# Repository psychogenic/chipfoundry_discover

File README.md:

# ChipFoundry ChipDiscover 2.0

ChipDiscover 2.0 is a mainboard designed to accept a variety of breakout modules (FPGA, TinyTapeout, Chipfoundry ASICs...) via an M.2 interface.

## FPGA M.2

The FPGA M.2 may be used along with [riffpga](https://github.com/psychogenic/riffpga) installed on the mainboard to allow for drag&drop bitstream loading through the USB-C connector and virtual drive.

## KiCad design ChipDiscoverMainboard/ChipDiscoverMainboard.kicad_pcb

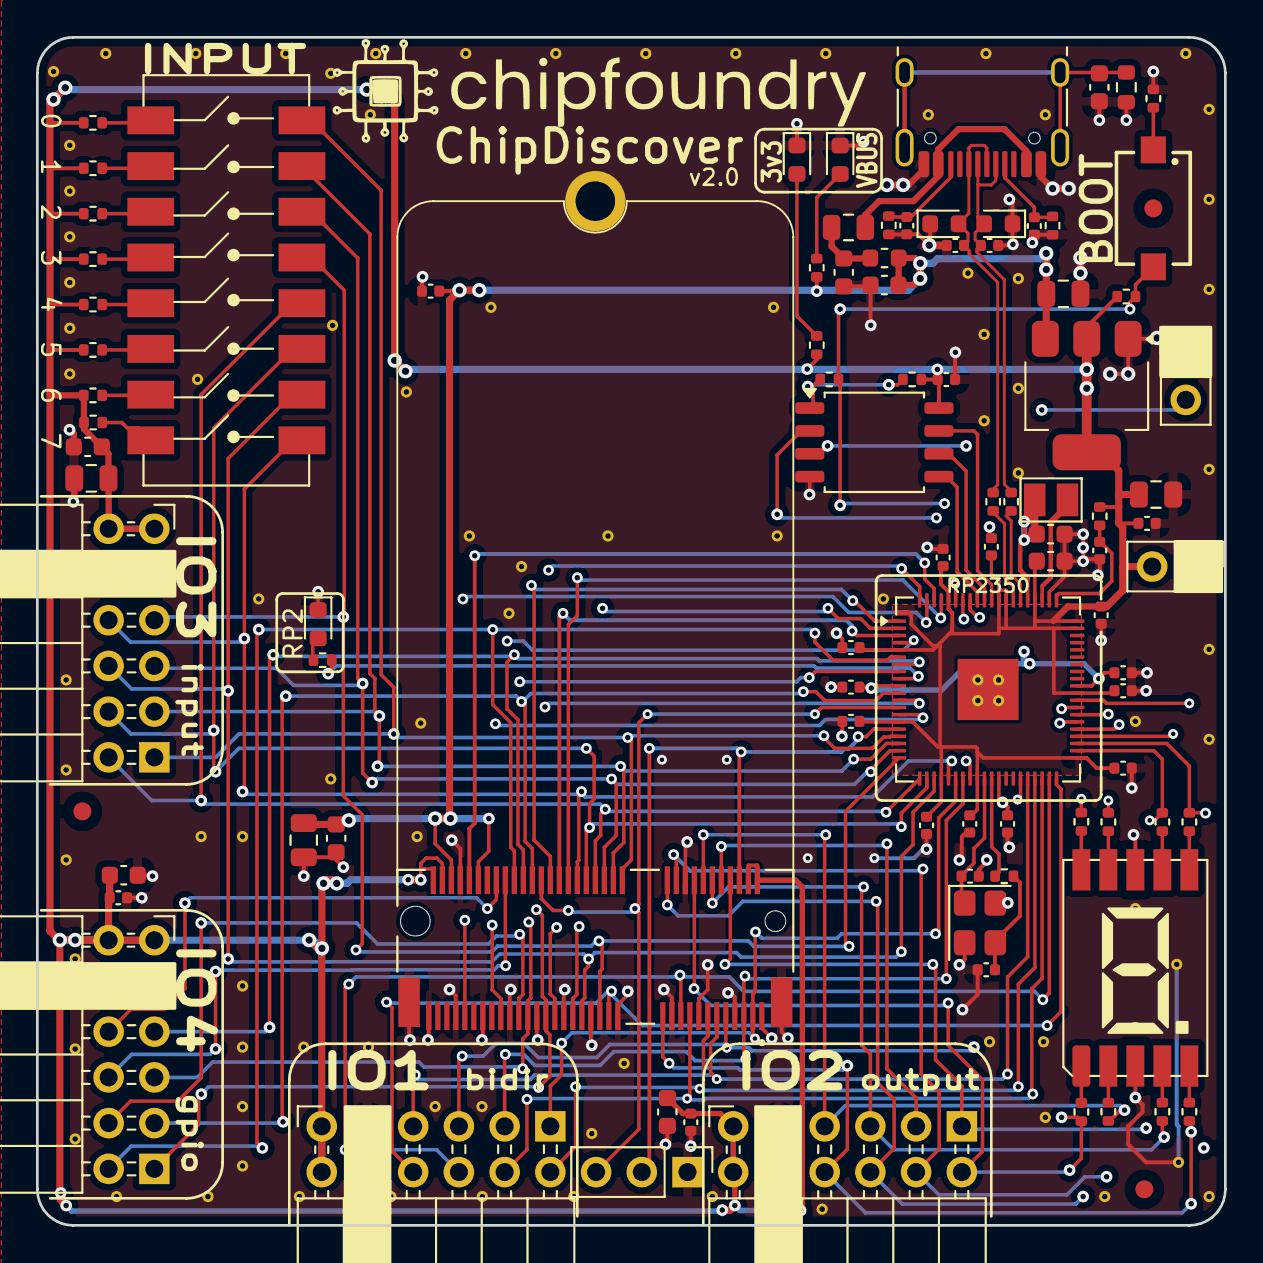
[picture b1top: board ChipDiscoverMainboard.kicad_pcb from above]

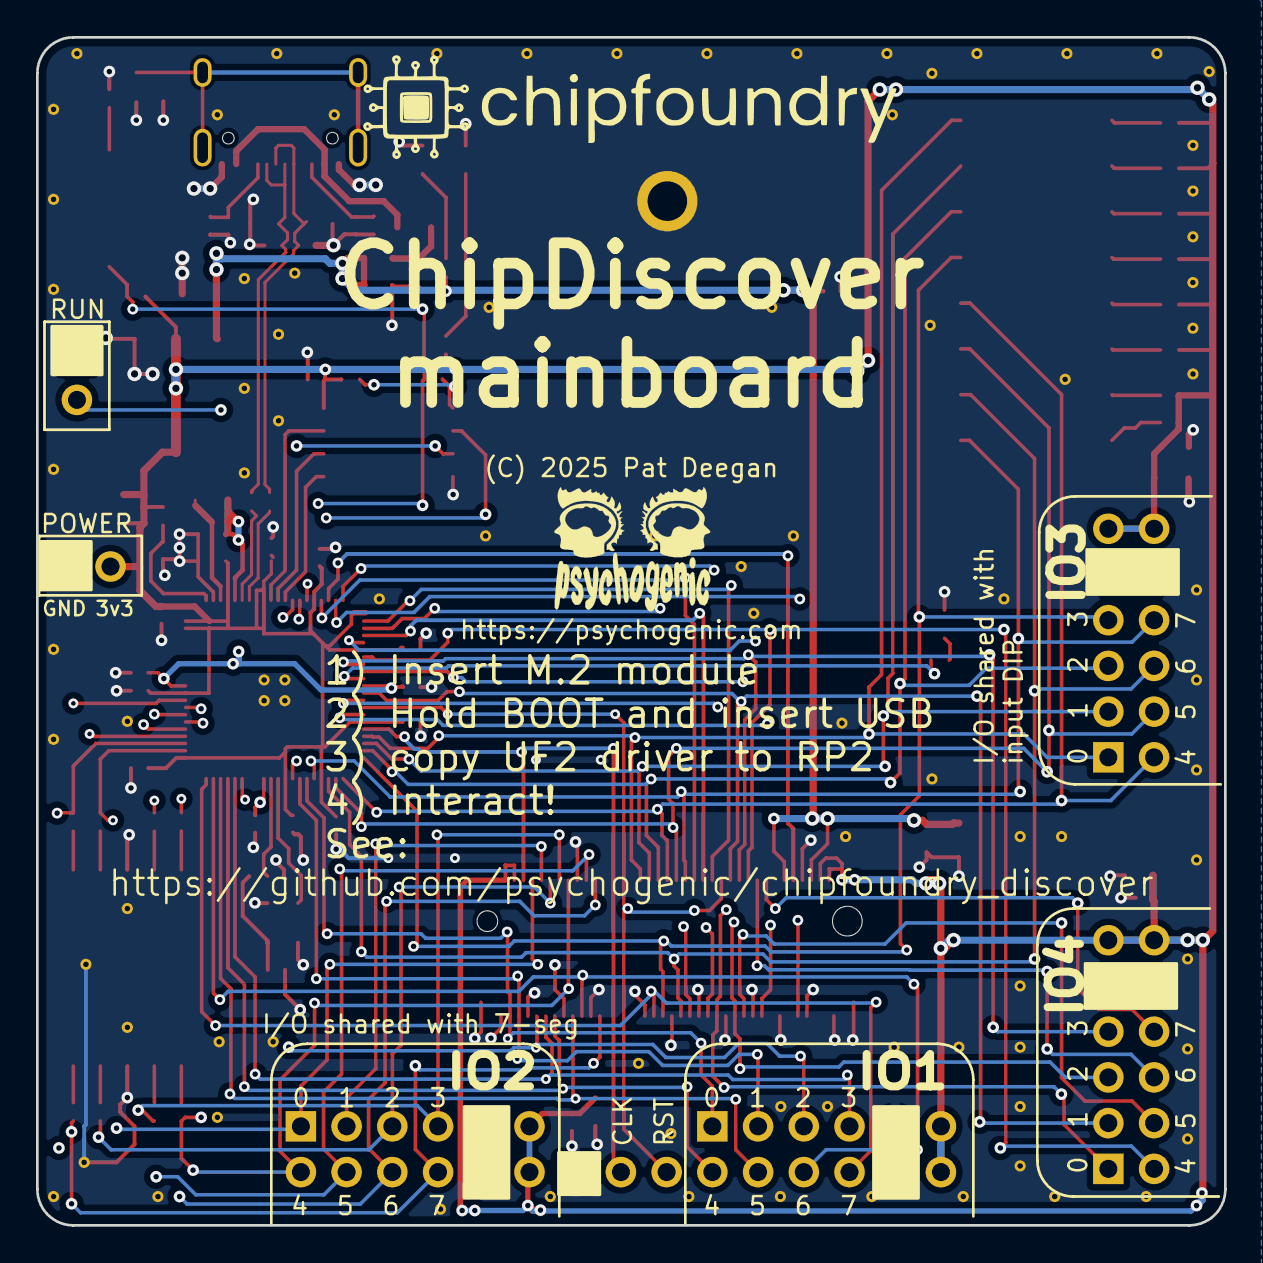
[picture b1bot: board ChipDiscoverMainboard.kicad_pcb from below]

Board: 4 copper layers, 66.0 x 66.0 mm, 188 parts (2 on the bottom side), 89 nets.

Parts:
C1, C2, C11, C13, C47, C49: 1uF; C_0603_1608Metric
C3, C10, C12: 10uF; C_0805_2012Metric
C4: 22uF; C_0805_2012Metric
C5, C14, C17, C19, C21, C22, C23, C24, C25, C26, C27, C28, C29, C30, C46, C48: 100n; C_0402_1005Metric
C6, C7, C8, C9: 33pF; C_0402_1005Metric
C15: 6800pF; C_0603_1608Metric
C16, C18: 14pF; C_0402_1005Metric
C20, C31: 4.7u; C_0402_1005Metric
C32, C33: 4.7u; C_0603_1608Metric
CHIPFNDRLOGO_LRG: LOGO; chipfoundry_logo_30mm
CHIPFNDRLOGO_LRG#2: LOGO; chipfoundry_logo_30mm
D1, D2: TVS; D_0603_1608Metric
D3, D6, D7: Yellow; LED_0603_1608Metric
F1: 350mA; Fuse_0805_2012Metric
FB1: 120R; L_0603_1608Metric
FID1, FID2, FID3: Fiducial; Fiducial_1mm_Mask2mm
J1: USB_C; USB_C_Receptacle_HRO_TYPE-C-31-M-12
J2, J9: Conn_01x02; PinHeader_1x02_P2.54mm_Vertical
J3: MDT320E01001; AMPHENOL_MDT320E01001
J4: M2SecuringHole; 2242-key-E_footprint
J6, J7, J18, J19: 613012243121; PinSocket_2x06_P2.54mm_PMODHost1A
J8: Conn_01x03; PinHeader_1x03_P2.54mm_Vertical
L1: 3.3u; L_2016X120N
PSYLOGO01: PSYLOGO; PsychoLogoSmall
R1, R2: 5.1k; R_0402_1005Metric
R3: 1M; R_0603_1608Metric
R4, R9: 10k; R_0402_1005Metric
R5, R10, R64, R65, R66, R67, R68, R69, R70, R71: 1k; R_0402_1005Metric
R6, R73, R74, R75, R76, R77, R78, R79, R80, R81: 510; R_0402_1005Metric
R7, R8: 27; R_0402_1005Metric
R11: 0; R_0402_1005Metric
R12: 33R; R_0402_1005Metric
R72: 1.2K; R_0402_1005Metric
STITCH01, STITCH01#2, STITCH01#3, STITCH01#4, STITCH01#5, STITCH01#6, STITCH01#7, STITCH01#8, STITCH01#9, STITCH01#10, STITCH01#11, STITCH01#12, STITCH01#13, STITCH01#14, STITCH01#15, STITCH01#16, STITCH01#17, STITCH01#18, STITCH01#19, STITCH01#20, STITCH01#21, STITCH01#22, STITCH01#23, STITCH01#24, STITCH01#25, STITCH01#26, STITCH01#27, STITCH01#28, STITCH01#29, STITCH01#30, STITCH01#31, STITCH01#32, STITCH01#33, STITCH01#34, STITCH01#35, STITCH01#36, STITCH01#37, STITCH01#38, STITCH01#39, STITCH01#40, STITCH01#41, STITCH01#42, STITCH01#43, STITCH01#44, STITCH01#45, STITCH01#46, STITCH01#47, STITCH01#48, STITCH01#49, STITCH01#50, STITCH01#51, STITCH2, STITCH3, STITCH4, STITCH5, STITCH6, STITCH7, STITCH8, STITCH9, STITCH10, STITCH10#2, STITCH11, STITCH12, STITCH13, STITCH14, STITCH16, STITCH17, STITCH18, STITCH19, STITCH21, STITCH22, STITCH22#2, STITCH23, STITCH24, STITCH25, STITCH26, STITCH26#2, STITCH27, STITCH28, STITCH29, STITCH30, STITCH31, STITCH32, STITCH33, STITCH34, STITCH35, STITCH36, STITCH37, STITCH38, STITCH39: StitchingVia-0.3mm
SW1: 434121025816
SW5: 193-8MSR; GENERIC_PIANO_8DIP
U1: TLV1117LV33; SOT-223-3_TabPin2
U2: RP2350-QFN80; QFN-80-1EP_10x10mm_P0.4mm_EP3.4x3.4mm
U3: W25Q32JVSS; SOIC-8_5.3x5.3mm_P1.27mm
U5: 157112V12700; WL_S7DS-157112V12700
Y1: 12.0MHz; Crystal_SMD_3225-4Pin_3.2x2.5mm

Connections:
+1V1: C19.1, C20.1, C21.1, C33.1, L1.1, U2.10 (DVDD), U2.32 (DVDD), U2.51 (DVDD), U2.65 (VREG_FB)
+3V3: C4.1, C5.1, C10.2, C11.2, C17.1, C22.1, C23.1, C24.1, C25.1, C26.1, C27.1, C28.1, C29.1, C30.1, C32.1, C46.1, C47.2, C48.1, C49.2, J3.2, J3.4, J3.72, J3.74, J6.6 (VCC), J6.12 (VCC), J7.6 (VCC), J7.12 (VCC), J9.2, J18.6 (VCC), J18.12 (VCC), J19.6 (VCC), J19.12 (VCC), R4.1, R9.1, R12.1, R64.1, R65.1, R66.1, R67.1, R68.1, R69.1, R70.1, R71.1, R73.1, U1.2 (VO), U2.5 (IOVDD), U2.15 (IOVDD), U2.24 (IOVDD), U2.29 (IOVDD), U2.41 (IOVDD), U2.50 (IOVDD), U2.59 (ADC_AVDD), U2.60 (IOVDD), U2.64 (VREG_VIN), U2.68 (USB_OTP_VDD), U2.69 (QSPI_IOVDD), U2.76 (IOVDD), U3.8 (VCC)
/BOOT: R4.2, R11.1, SW1.2, U2.75 (QSPI_SS)
/CC1: C6.1, J1.A5 (CC1), R2.1
/CC2: C7.1, J1.B5 (CC2), R1.1
/MSPI.MISO: J3.48, U2.1 (GPIO4)
/MSPI.MOSI: J3.47, U2.80 (GPIO3)
/MSPI.SCK: J3.46, U2.3 (GPIO6)
/MSPI.~SS: J3.43, U2.2 (GPIO5)
/RP2350/CLKIN: C16.1, U2.30 (XIN), Y1.1
/RP2350/CLKO2: C18.1, R10.2, Y1.3
/RP2350/CLKOUT: R10.1, U2.31 (XOUT)
/RP2350/FLASH_SS: R9.2, R11.2, U3.1 (~CS)
/RP2350/QSPI_SCK: U2.71 (QSPI_SCLK), U3.6 (CLK)
/RP2350/QSPI_SD0: U2.72 (QSPI_SD0), U3.5 (DI(IO0))
/RP2350/QSPI_SD1: U2.74 (QSPI_SD1), U3.2 (DO(IO1))
/RP2350/QSPI_SD2: U2.73 (QSPI_SD2), U3.3 (IO2)
/RP2350/QSPI_SD3: U2.70 (QSPI_SD3), U3.7 (IO3)
/RP2350/USBPi_+: R7.2, U2.67 (USB_DP)
/RP2350/USBPi_-: R8.2, U2.66 (USB_DM)
/RP2350/VREG_AVDD: C31.1, R12.2, U2.61 (VREG_AVDD)
/RP2350/VREG_LX: L1.2, U2.63 (VREG_LX)
/RPLED: R6.1, U2.9 (GPIO11)
/RUN: J2.2, U2.35 (RUN)
/chip_rst: J3.59, U2.14 (GPIO15)
/ctrl_ena: J3.44, U2.77 (GPIO0)
/ctrl_sel_inc: J3.67, U2.79 (GPIO2)
/gp0: J3.49, J7.1 (IO1), U2.12 (GPIO13)
/gp1: J3.52, J7.2 (IO2), U2.11 (GPIO12)
/gp2: J3.53, J7.3 (IO3), U2.8 (GPIO10)
/gp3: J3.54, J7.4 (IO4), U2.7 (GPIO9)
/gp4: J3.56, J7.7 (IO5), U2.6 (GPIO8)
/gp5: J3.55, J7.8 (IO6), U2.4 (GPIO7)
/gp6: J3.58, J7.9 (IO7)
/gp7: J3.60, J7.10 (IO8)
/prj_clk: J3.6, J8.2, U2.16 (GPIO16)
/prj_~rst: J3.50, J8.3, U2.13 (GPIO14)
/ui_in0: J3.32, J6.1 (IO1), SW5.16, U2.17 (GPIO17)
/ui_in1: J3.34, J6.2 (IO2), SW5.15, U2.18 (GPIO18)
/ui_in2: J3.36, J6.3 (IO3), SW5.14, U2.19 (GPIO19)
/ui_in3: J3.37, J6.4 (IO4), SW5.13, U2.20 (GPIO20)
/ui_in4: J3.38, J6.7 (IO5), SW5.12, U2.21 (GPIO21)
/ui_in5: J3.40, J6.8 (IO6), SW5.11, U2.22 (GPIO22)
/ui_in6: J3.41, J6.9 (IO7), SW5.10, U2.23 (GPIO23)
/ui_in7: J3.42, J6.10 (IO8), SW5.9, U2.25 (GPIO24)
/uio0: J3.3, J18.1 (IO1), U2.26 (GPIO25)
/uio1: J3.5, J18.2 (IO2), U2.27 (GPIO26)
/uio2: J3.9, J18.3 (IO3), U2.28 (GPIO27)
/uio3: J3.11, J18.4 (IO4), U2.36 (GPIO28)
/uio4: J3.13, J18.7 (IO5), U2.37 (GPIO29)
/uio5: J3.17, J18.8 (IO6), U2.38 (GPIO30)
/uio6: J3.19, J18.9 (IO7), U2.39 (GPIO31)
/uio7: J3.35, J18.10 (IO8), U2.40 (GPIO32)
/uo_out0: J3.8, J19.1 (IO1), R74.1, U2.42 (GPIO33)
/uo_out1: J3.10, J19.2 (IO2), R75.1, U2.43 (GPIO34)
/uo_out2: J3.12, J19.3 (IO3), R76.1, U2.44 (GPIO35)
/uo_out3: J3.14, J19.4 (IO4), R77.1, U2.45 (GPIO36)
/uo_out4: J3.16, J19.7 (IO5), R78.1, U2.46 (GPIO37)
/uo_out5: J3.20, J19.8 (IO6), R79.1, U2.47 (GPIO38)
/uo_out6: J3.22, J19.9 (IO7), R80.1, U2.48 (GPIO39)
/uo_out7: J3.23, J19.10 (IO8), R81.1, U2.49 (GPIO40_ADC0)
/vfused: C1.1, F1.2, FB1.1
/~ctrl_sel_rst: J3.66, U2.78 (GPIO1)
GND: C1.2, C2.2, C3.2, C4.2, C5.2, C6.2, C7.2, C8.2, C9.2, C10.1, C11.1, C12.1, C13.1, C14.1, C15.2, C16.2, C17.2, C18.2, C19.2, C20.2, C21.2, C22.2, C23.2, C24.2, C25.2, C26.2, C27.2, C28.2, C29.2, C30.2, C31.2, C32.2, C33.2, C46.2, C47.1, C48.2, C49.1, D1.1 (A1), D2.1 (A1), D3.1 (K), D6.1 (K), D7.1 (K), J1.A1 (GND), J1.A12 (GND), J1.B1 (GND), J1.B12 (GND), J2.1, J3.1, J3.7, J3.15, J3.18, J3.21, J3.33, J3.39, J3.45, J3.51, J3.57, J3.63, J3.68, J3.69, J3.75, J3.S1 (SHIELD), J3.S2 (SHIELD), J4.1, J6.5 (GND), J6.11 (GND), J7.5 (GND), J7.11 (GND), J8.1, J9.1, J18.5 (GND), J18.11 (GND), J19.5 (GND), J19.11 (GND), R1.2, R2.2, R3.2, R5.2, STITCH01.1, STITCH01#2.1, STITCH01#3.1, STITCH01#4.1, STITCH01#5.1, STITCH01#6.1, STITCH01#7.1, STITCH01#8.1, STITCH01#9.1, STITCH01#10.1, STITCH01#11.1, STITCH01#12.1, STITCH01#13.1, STITCH01#14.1, STITCH01#15.1, STITCH01#16.1, STITCH01#17.1, STITCH01#18.1, STITCH01#19.1, STITCH01#20.1, STITCH01#21.1, STITCH01#22.1, STITCH01#23.1, STITCH01#24.1, STITCH01#25.1, STITCH01#26.1, STITCH01#27.1, STITCH01#28.1, STITCH01#29.1, STITCH01#30.1, STITCH01#31.1, STITCH01#32.1, STITCH01#33.1, STITCH01#34.1, STITCH01#35.1, STITCH01#36.1, STITCH01#37.1, STITCH01#38.1, STITCH01#39.1, STITCH01#40.1, STITCH01#41.1, STITCH01#42.1, STITCH01#43.1, STITCH01#44.1, STITCH01#45.1, STITCH01#46.1, STITCH01#47.1, STITCH01#48.1, STITCH01#49.1, STITCH01#50.1, STITCH01#51.1, STITCH2.1, STITCH3.1, STITCH4.1, STITCH5.1, STITCH6.1, STITCH7.1, STITCH8.1, STITCH9.1, STITCH10.1, STITCH10#2.1, STITCH11.1, STITCH12.1, STITCH13.1, STITCH14.1, STITCH16.1, STITCH17.1, STITCH18.1, STITCH19.1, STITCH21.1, STITCH22.1, STITCH22#2.1, STITCH23.1, STITCH24.1, STITCH25.1, STITCH26.1, STITCH26#2.1, STITCH27.1, STITCH28.1, STITCH29.1, STITCH30.1, STITCH31.1, STITCH32.1, STITCH33.1, STITCH34.1, STITCH35.1, STITCH36.1, STITCH37.1, STITCH38.1, STITCH39.1, U1.1 (GND), U2.62 (VREG_PGND), U2.81 (GND), U3.4 (GND), U5.3 (CC), U5.8 (CC), Y1.2, Y1.4
unnamed: D3.2 (A), R6.2
unnamed: D6.2 (A), R72.2
unnamed: D7.2 (A), R73.2
unnamed: C15.1, J1.S1 (SHIELD), R3.1
unnamed: R5.1, SW1.1
unnamed: R64.2, SW5.1
unnamed: R65.2, SW5.2
unnamed: R66.2, SW5.3
unnamed: R67.2, SW5.4
unnamed: R68.2, SW5.5
unnamed: R69.2, SW5.6
unnamed: R70.2, SW5.7
unnamed: R71.2, SW5.8
unnamed: R74.2, U5.7 (A)
unnamed: R75.2, U5.6 (B)
unnamed: R76.2, U5.4 (C)
unnamed: R77.2, U5.2 (D)
unnamed: R81.2, U5.5 (DP)
unnamed: R78.2, U5.1 (E)
unnamed: R79.2, U5.9 (F)
unnamed: R80.2, U5.10 (G)
VBUS: C2.1, C3.1, C12.2, C13.2, C14.2, FB1.2, J3.64, J3.70, R72.1, U1.3 (VI)
VBUSRW: F1.1, J1.A4 (VBUS), J1.A9 (VBUS), J1.B4 (VBUS), J1.B9 (VBUS)
usb_d+: C9.1, D2.2 (A2), J1.A6 (D+), J1.B6 (D+), R7.1
usb_d-: C8.1, D1.2 (A2), J1.A7 (D-), J1.B7 (D-), R8.1

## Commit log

2026-06-13 initial import

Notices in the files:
ChipDiscoverMainboard/ChipDiscoverMainboard.kicad_pcb:
(C) 2025 Pat Deegan
